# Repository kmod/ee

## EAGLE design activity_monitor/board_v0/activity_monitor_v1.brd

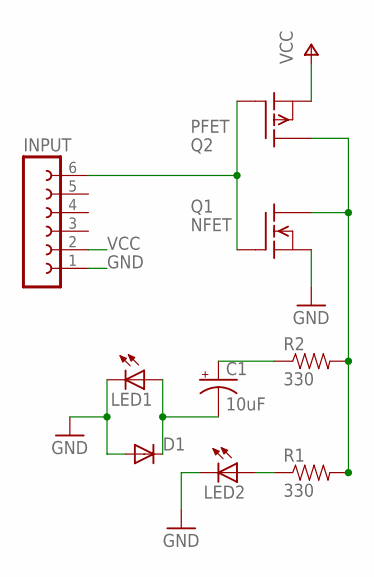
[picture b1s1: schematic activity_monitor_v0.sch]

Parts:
C1: 10uF; CPOL-RADIAL-10UF-25V
D1: 1N4004; DO41-10
INPUT: FE06-1; FE06
LED1, LED2: LED5MM
Q1: NFET; TO220
Q2: PFET; TO220
R1, R2: 330; AXIAL-0.3

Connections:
44: INPUT.6, Q1.1 (G), Q2.1 (G)
GND: D1.A, INPUT.1, LED1.K (C), LED2.K (C), Q1.3 (S)
unnamed: LED2.A, R1.P$1 (1)
unnamed: C1.1 (+), R2.P$1 (1)
unnamed: C1.2 (-), D1.C, LED1.A
unnamed: Q1.2 (D), Q2.2 (D), R1.P$2 (2), R2.P$2 (2)
VCC: INPUT.2, Q2.3 (S)

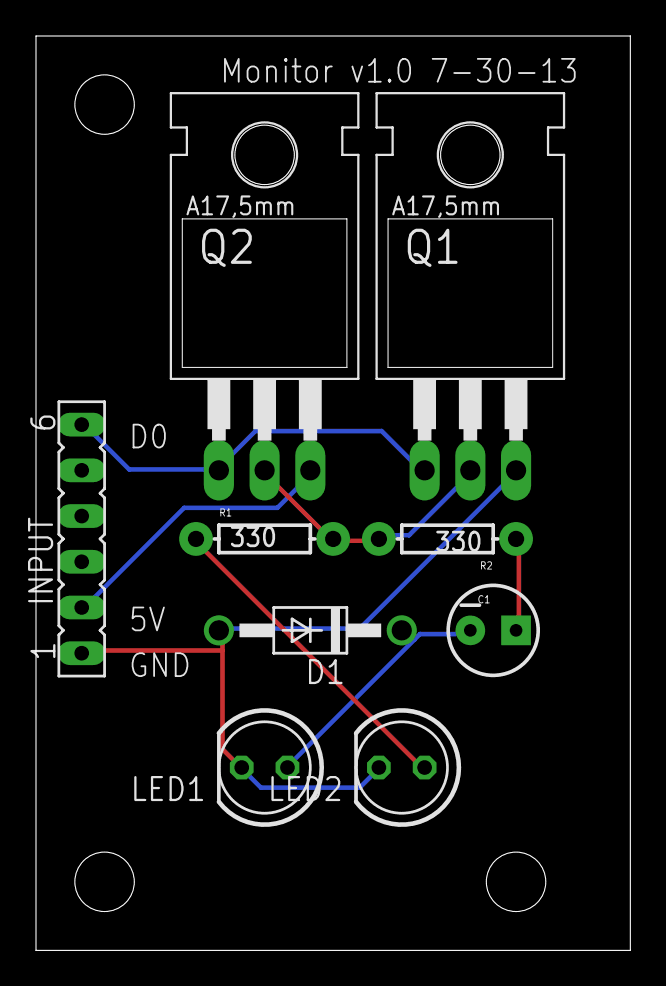
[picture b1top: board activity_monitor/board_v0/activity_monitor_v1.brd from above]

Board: 2 copper layers, 33.0 x 50.8 mm, 12 parts (0 on the bottom side), 7 nets.

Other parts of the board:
U$1, U$2, U$3: STAND-OFF

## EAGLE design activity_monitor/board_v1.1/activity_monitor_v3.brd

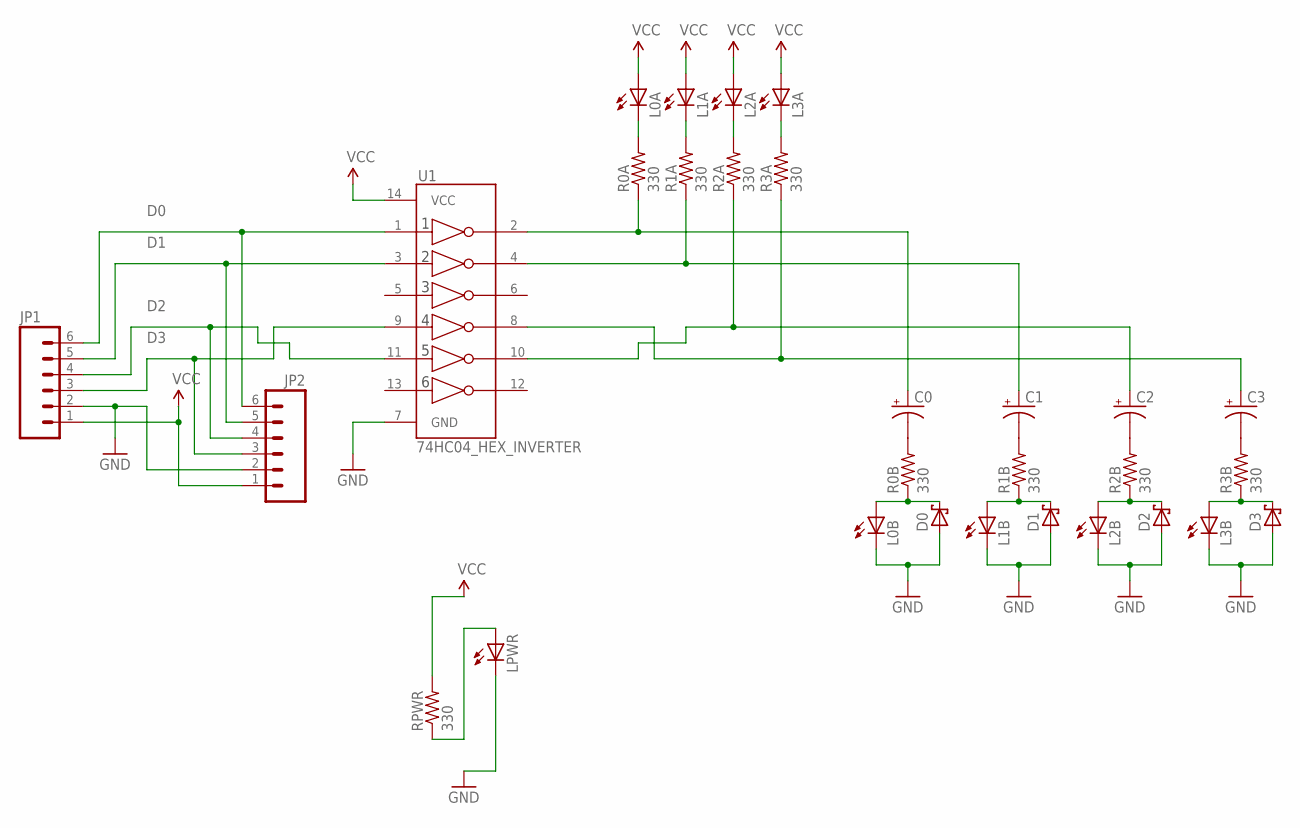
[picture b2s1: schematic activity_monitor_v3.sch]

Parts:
C0, C1, C2, C3: 10UF-TANT; EIA3216
D0, D1, D2, D3: SCHOTTKY-DIODEDO35-7; DO35-7
JP1, JP2: M06SIP; 1X06
L0A, L0B, L1A, L1B, L2A, L2B, L3A, L3B: LED0603; LED-0603
LPWR: LED0603; LED-0603
R0A, R0B, R1A, R1B, R2A, R2B, R3A, R3B: 330; 0603-RES
RPWR: 330; 0603-RES
U1: 74HC04_HEX_INVERTER; DIL14

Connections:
D0: JP1.6, JP2.6, U1.1 (1A)
D1: JP1.5, JP2.5, U1.3 (2A)
D2: JP1.4, JP2.4, U1.11 (5A)
D3: JP1.3, JP2.3, U1.9 (4A)
GND: D0.A, D1.A, D2.A, D3.A, JP1.2, JP2.2, L0B.C, L1B.C, L2B.C, L3B.C, LPWR.C, U1.7 (GND)
unnamed: C0.A (+), R0A.1, U1.2 (1Y)
unnamed: C1.A (+), R1A.1, U1.4 (2Y)
unnamed: C2.A (+), R2A.1, U1.10 (5Y)
unnamed: C3.A (+), R3A.1, U1.8 (4Y)
unnamed: L0A.C, R0A.2
unnamed: L1A.C, R1A.2
unnamed: L2A.C, R2A.2
unnamed: L3A.C, R3A.2
unnamed: C0.C (-), R0B.2
unnamed: D0.C, L0B.A, R0B.1
unnamed: C1.C (-), R1B.2
unnamed: LPWR.A, RPWR.1
unnamed: C2.C (-), R2B.2
unnamed: C3.C (-), R3B.2
R1B: D1.C, L1B.A, R1B.1
R2B: D2.C, L2B.A, R2B.1
R3B: D3.C, L3B.A, R3B.1
VCC: JP1.1, JP2.1, L0A.A, L1A.A, L2A.A, L3A.A, RPWR.2, U1.14 (VCC)

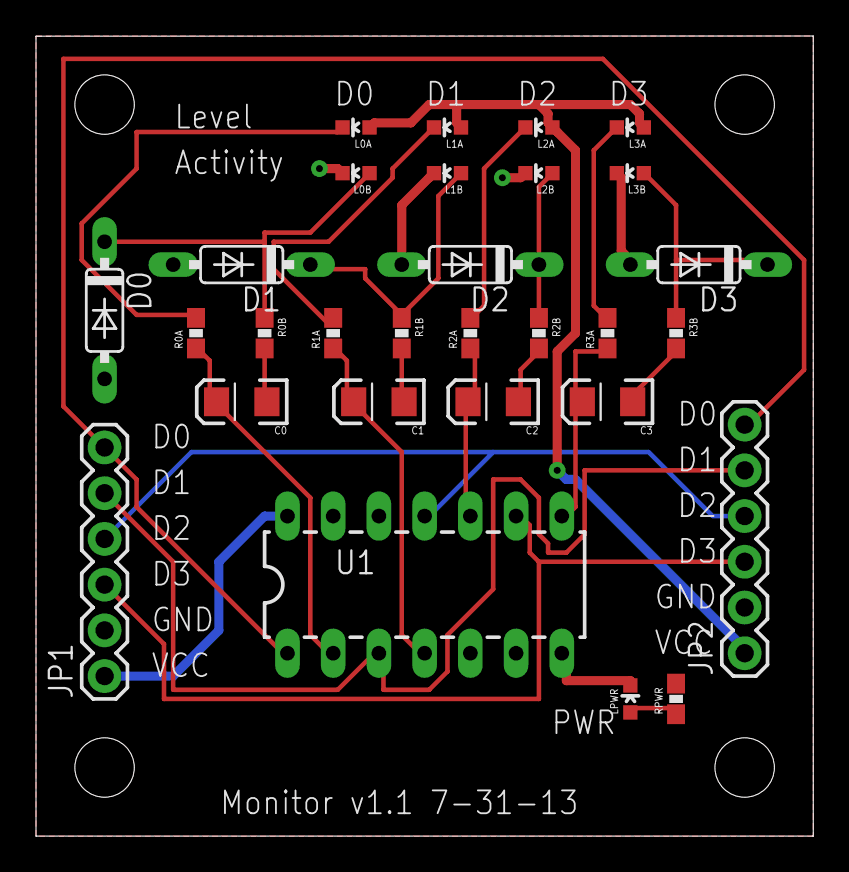
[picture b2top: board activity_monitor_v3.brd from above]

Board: 2 copper layers, 43.2 x 44.5 mm, 33 parts (0 on the bottom side), 23 nets.

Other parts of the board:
U$1, U$2, U$3, U$4: STAND-OFF

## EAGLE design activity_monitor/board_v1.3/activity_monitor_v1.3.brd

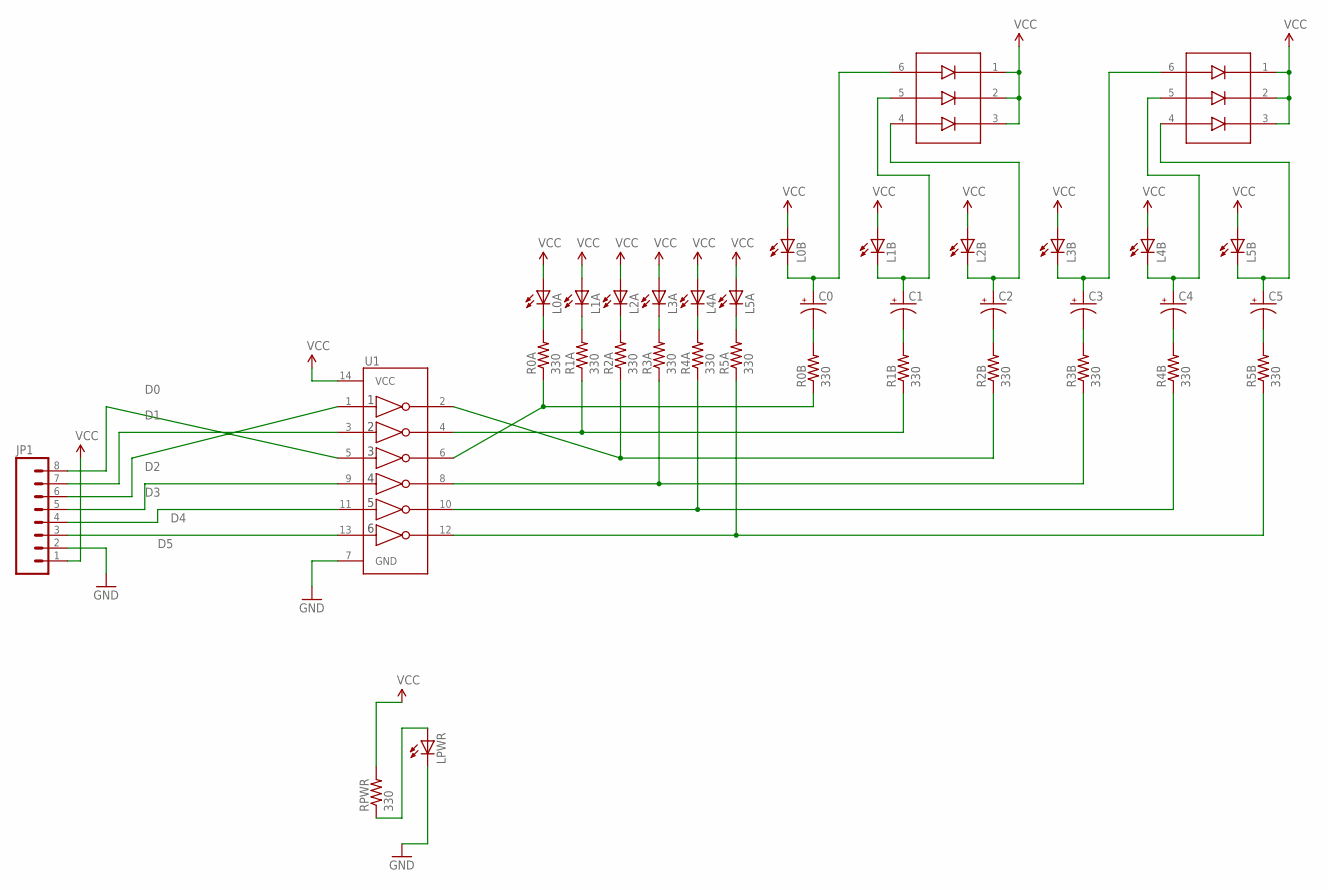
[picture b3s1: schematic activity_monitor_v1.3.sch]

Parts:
C0, C1, C2, C3, C4, C5: 10UF-TANT; EIA3216
JP1: M081X08; 1X08
L0A, L0B, L1A, L1B, L2A, L2B, L3A, L3B, L4A, L4B, L5A, L5B: LED0603; 0603_LED
LPWR: LED0603; 0603_LED
R0A, R0B, R1A, R1B, R2A, R2B, R3A, R3B, R4A, R4B, R5A, R5B: 330; 0603-RES
RPWR: 330; 0603-RES
U1: 74HC04_HEX_INVERTERTSSOP14; TSSOP14
U$1, U$2: SD103ATW-7-F; SOT363

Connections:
D0: JP1.8, U1.5 (3A)
D1: JP1.7, U1.3 (2A)
D2: JP1.6, U1.1 (1A)
D3: JP1.5, U1.9 (4A)
D4: JP1.4, U1.11 (5A)
D5: JP1.3, U1.13 (6A)
GND: JP1.2, LPWR.C, U1.7 (GND)
unnamed: R0A.1, R0B.1, U1.6 (3Y)
unnamed: R1A.1, R1B.1, U1.4 (2Y)
unnamed: C5.C (-), R5B.2
unnamed: C4.C (-), R4B.2
unnamed: L0A.C, R0A.2
unnamed: L1A.C, R1A.2
unnamed: L2A.C, R2A.2
unnamed: L3A.C, R3A.2
unnamed: C3.C (-), R3B.2
unnamed: C0.A (+), L0B.C, U$1.6 (I1)
unnamed: L4A.C, R4A.2
unnamed: C2.C (-), R2B.2
unnamed: LPWR.A, RPWR.1
unnamed: L5A.C, R5A.2
unnamed: C1.C (-), R1B.2
unnamed: R2A.1, R2B.1, U1.2 (1Y)
unnamed: R3A.1, R3B.1, U1.8 (4Y)
unnamed: C0.C (-), R0B.2
unnamed: R4A.1, R4B.1, U1.10 (5Y)
unnamed: R5A.1, R5B.1, U1.12 (6Y)
unnamed: C1.A (+), L1B.C, U$1.5 (I2)
unnamed: C2.A (+), L2B.C, U$1.4 (I3)
unnamed: C3.A (+), L3B.C, U$2.6 (I1)
unnamed: C4.A (+), L4B.C, U$2.5 (I2)
unnamed: C5.A (+), L5B.C, U$2.4 (I3)
VCC: JP1.1, L0A.A, L0B.A, L1A.A, L1B.A, L2A.A, L2B.A, L3A.A, L3B.A, L4A.A, L4B.A, L5A.A, L5B.A, RPWR.2, U1.14 (VCC), U$1.1 (O1), U$1.2 (O2), U$1.3 (O3), U$2.1 (O1), U$2.2 (O2), U$2.3 (O3)

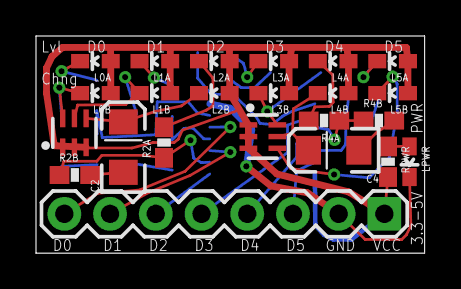
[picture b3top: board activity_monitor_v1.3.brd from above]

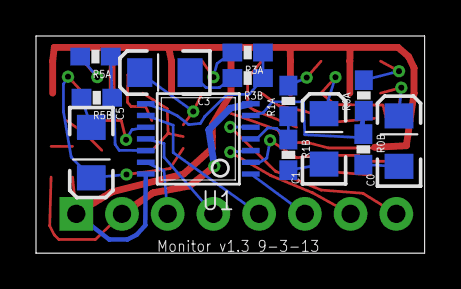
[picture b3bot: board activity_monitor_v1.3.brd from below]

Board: 2 copper layers, 21.6 x 12.1 mm, 36 parts (13 on the bottom side), 33 nets.

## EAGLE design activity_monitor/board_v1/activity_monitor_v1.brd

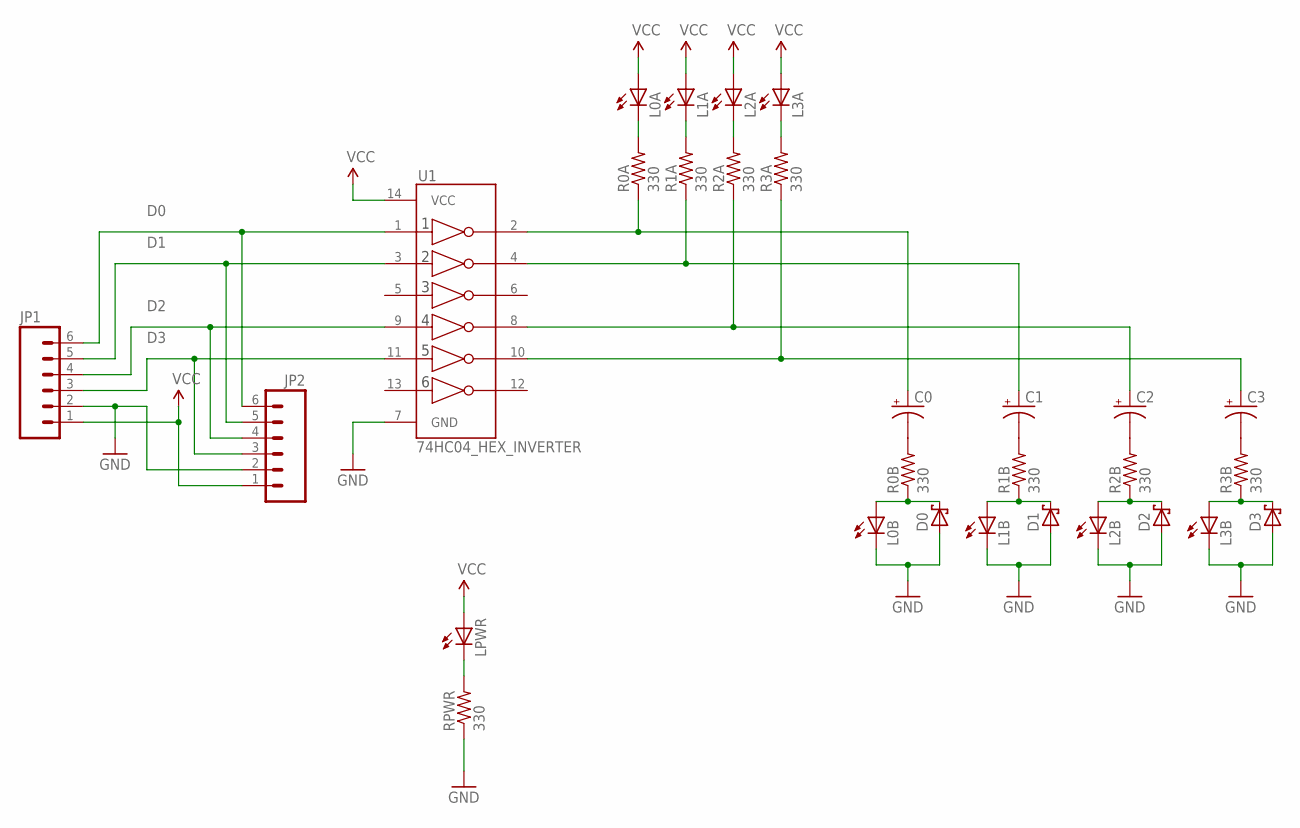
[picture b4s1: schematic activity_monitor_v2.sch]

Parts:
C0, C1, C2, C3: CAP_POLPTH2; CPOL-RADIAL-10UF-25V
D0, D1, D2, D3: SCHOTTKY-DIODEDO35-7; DO35-7
JP1, JP2: M06SIP; 1X06
L0A, L0B, L1A, L1B, L2A, L2B, L3A, L3B: LED3MM
LPWR: LED3MM
R0A, R0B, R1A, R1B, R2A, R2B, R3A, R3B: 330; AXIAL-0.4
RPWR: 330; AXIAL-0.4
U1: 74HC04_HEX_INVERTER; DIL14

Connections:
D0: JP1.6, JP2.6, U1.1 (1A)
D1: JP1.5, JP2.5, U1.3 (2A)
D2: JP1.4, JP2.4, U1.9 (4A)
D3: JP1.3, JP2.3, U1.11 (5A)
GND: D0.A, D1.A, D2.A, D3.A, JP1.2, JP2.2, L0B.K (C), L1B.K (C), L2B.K (C), L3B.K (C), RPWR.P$1 (1), U1.7 (GND)
unnamed: C0.1 (+), R0A.P$1 (1), U1.2 (1Y)
unnamed: C1.1 (+), R1A.P$1 (1), U1.4 (2Y)
unnamed: C2.1 (+), R2A.P$1 (1), U1.8 (4Y)
unnamed: C3.1 (+), R3A.P$1 (1), U1.10 (5Y)
unnamed: L0A.K (C), R0A.P$2 (2)
unnamed: L1A.K (C), R1A.P$2 (2)
unnamed: L2A.K (C), R2A.P$2 (2)
unnamed: L3A.K (C), R3A.P$2 (2)
unnamed: C0.2 (-), R0B.P$2 (2)
unnamed: D0.C, L0B.A, R0B.P$1 (1)
unnamed: C1.2 (-), R1B.P$2 (2)
unnamed: LPWR.K (C), RPWR.P$2 (2)
unnamed: C2.2 (-), R2B.P$2 (2)
unnamed: C3.2 (-), R3B.P$2 (2)
R1B: D1.C, L1B.A, R1B.P$1 (1)
R2B: D2.C, L2B.A, R2B.P$1 (1)
R3B: D3.C, L3B.A, R3B.P$1 (1)
VCC: JP1.1, JP2.1, L0A.A, L1A.A, L2A.A, L3A.A, LPWR.A, U1.14 (VCC)

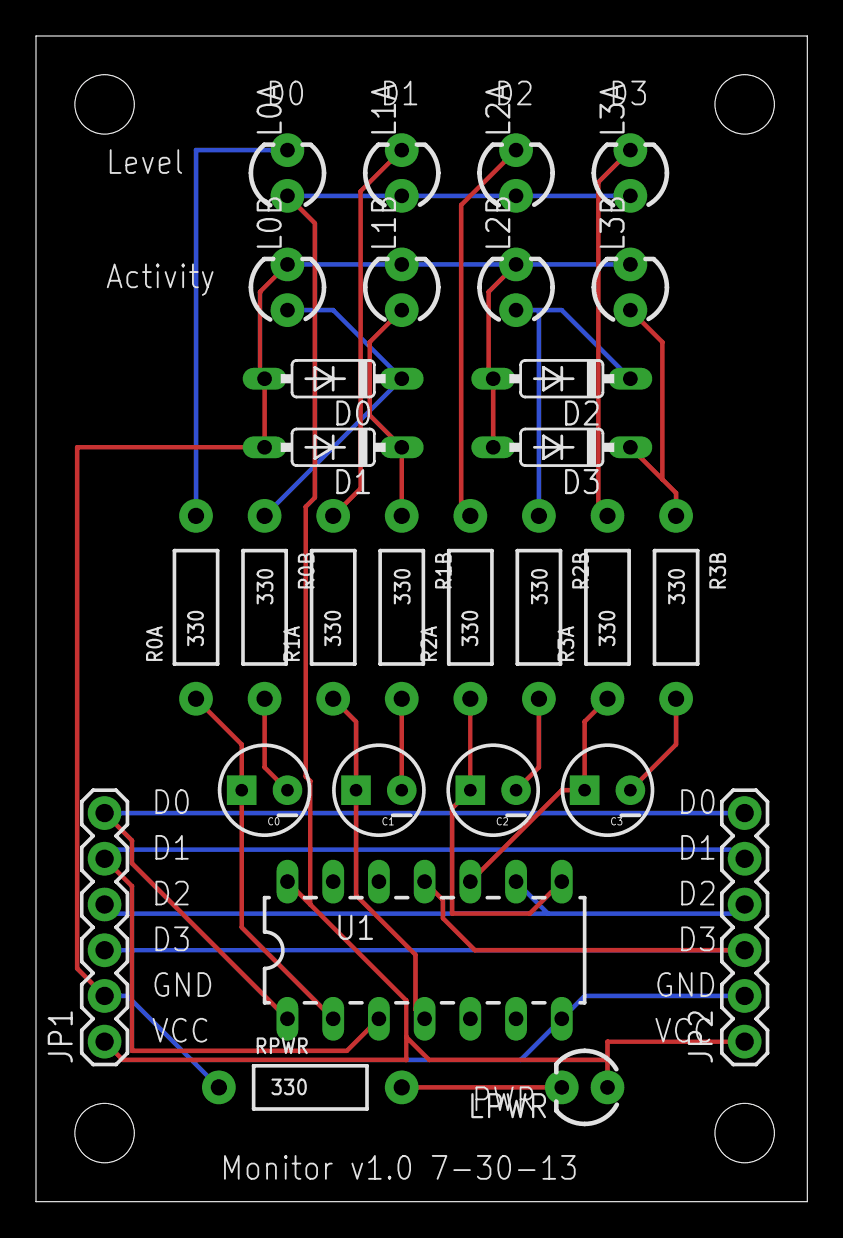
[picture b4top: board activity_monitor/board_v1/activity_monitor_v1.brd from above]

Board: 2 copper layers, 42.9 x 64.8 mm, 33 parts (0 on the bottom side), 23 nets.

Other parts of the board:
U$1, U$2, U$3, U$4: STAND-OFF

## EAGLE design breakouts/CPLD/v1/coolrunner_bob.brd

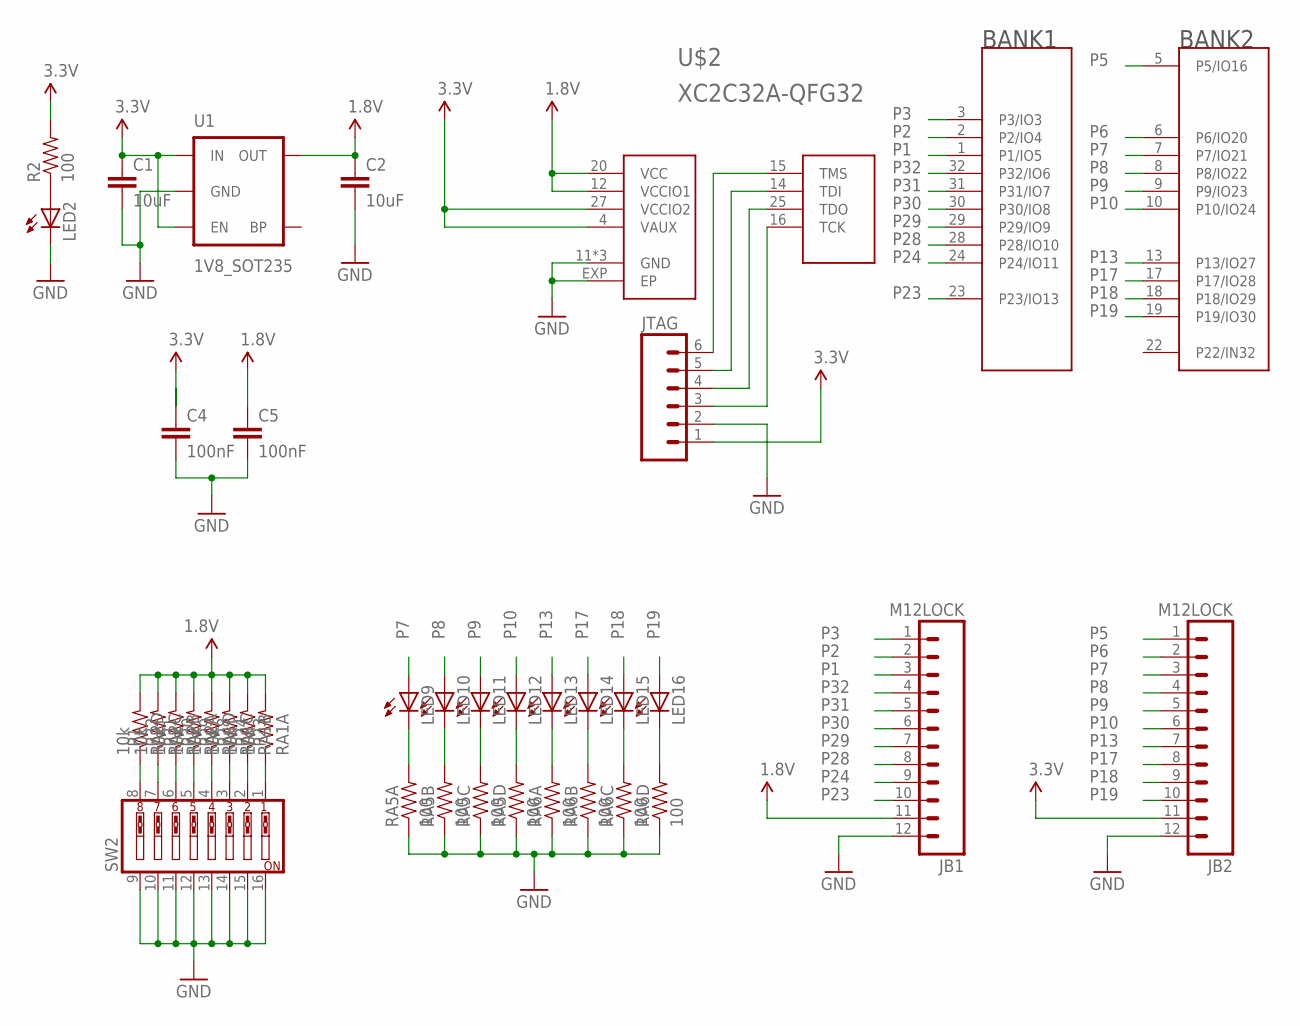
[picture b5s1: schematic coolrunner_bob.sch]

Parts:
C1, C2: 10uF; 0805
C4, C5: 100nF; 0402-CAP
JB1, JB2: M12LOCK; 1X12_LOCK
JTAG: M06LOCK; 1X06_LOCK
LED2, LED9, LED10, LED11, LED12, LED13, LED14, LED15, LED16: LED0603; LED-0603
R2: 100; 0603-RES
RA1, RA2: 10k; 0603-ARV
RA5, RA6: 100; 0603-ARV
SW2: SW_DIP-8; DIPSWITCH-08
U1: 1V8_SOT235; SOT23-5
U$2: XC2C32A-QFG32; QFN32-5X5

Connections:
1.8V: C2.1, C5.1, JB1.11, RA1.5 (2), RA1.6 (2), RA1.7 (2), RA1.8 (2), RA2.5 (2), RA2.6 (2), RA2.7 (2), RA2.8 (2), U1.5 (OUT), U$2.12 (VCCIO1), U$2.20 (VCC)
3.3V: C1.1, C4.1, JB2.11, JTAG.1, R2.2, U1.1 (IN), U1.3 (EN), U$2.4 (VAUX), U$2.27 (VCCIO2)
GND: C1.2, C2.2, C4.2, C5.2, JB1.12, JB2.12, JTAG.2, LED2.C, RA5.1, RA5.2 (1), RA5.3 (1), RA5.4 (1), RA6.1, RA6.2 (1), RA6.3 (1), RA6.4 (1), SW2.9, SW2.10, SW2.11, SW2.12, SW2.13, SW2.14, SW2.15, SW2.16, U1.2 (GND), U$2.11 (GND), U$2.21 (GND), U$2.26 (GND), U$2.EXP (EP)
unnamed: LED2.A, R2.1
unnamed: LED16.C, RA6.5 (2)
unnamed: LED15.C, RA6.6 (2)
unnamed: LED14.C, RA6.7 (2)
unnamed: LED13.C, RA6.8 (2)
unnamed: LED12.C, RA5.5 (2)
unnamed: LED11.C, RA5.6 (2)
unnamed: LED10.C, RA5.7 (2)
unnamed: LED9.C, RA5.8 (2)
P1: JB1.3, RA2.4 (1), SW2.8, U$2.1 (P1/IO5)
P2: JB1.2, U$2.2 (P2/IO4)
P3: JB1.1, U$2.3 (P3/IO3)
P5: JB2.1, U$2.5 (P5/IO16)
P6: JB2.2, U$2.6 (P6/IO20)
P7: JB2.3, LED9.A, U$2.7 (P7/IO21)
P8: JB2.4, LED10.A, U$2.8 (P8/IO22)
P9: JB2.5, LED11.A, U$2.9 (P9/IO23)
P10: JB2.6, LED12.A, U$2.10 (P10/IO24)
P13: JB2.7, LED13.A, U$2.13 (P13/IO27)
P17: JB2.8, LED14.A, U$2.17 (P17/IO28)
P18: JB2.9, LED15.A, U$2.18 (P18/IO29)
P19: JB2.10, LED16.A, U$2.19 (P19/IO30)
P23: JB1.10, RA1.1, SW2.1, U$2.23 (P23/IO13)
P24: JB1.9, RA1.2 (1), SW2.2, U$2.24 (P24/IO11)
P28: JB1.8, RA1.3 (1), SW2.3, U$2.28 (P28/IO10)
P29: JB1.7, RA1.4 (1), SW2.4, U$2.29 (P29/IO9)
P30: JB1.6, RA2.1, SW2.5, U$2.30 (P30/IO8)
P31: JB1.5, RA2.2 (1), SW2.6, U$2.31 (P31/IO7)
P32: JB1.4, RA2.3 (1), SW2.7, U$2.32 (P32/IO6)
TCK: JTAG.3, U$2.16 (TCK)
TDI: JTAG.5, U$2.14 (TDI)
TDO: JTAG.4, U$2.25 (TDO)
TMS: JTAG.6, U$2.15 (TMS)

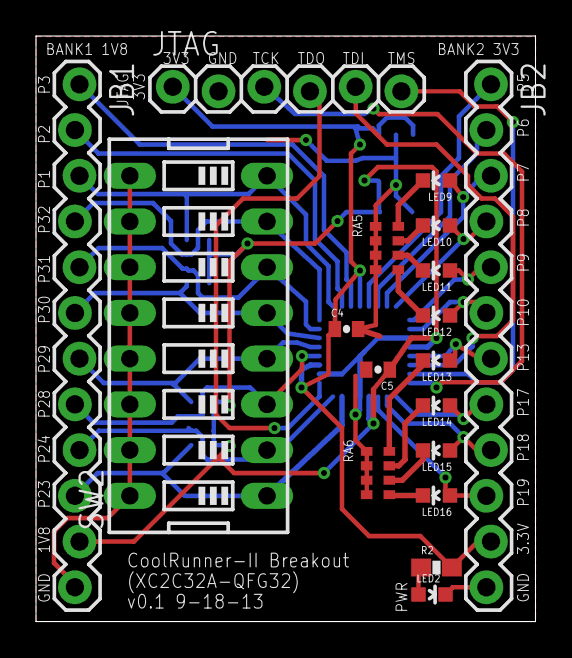
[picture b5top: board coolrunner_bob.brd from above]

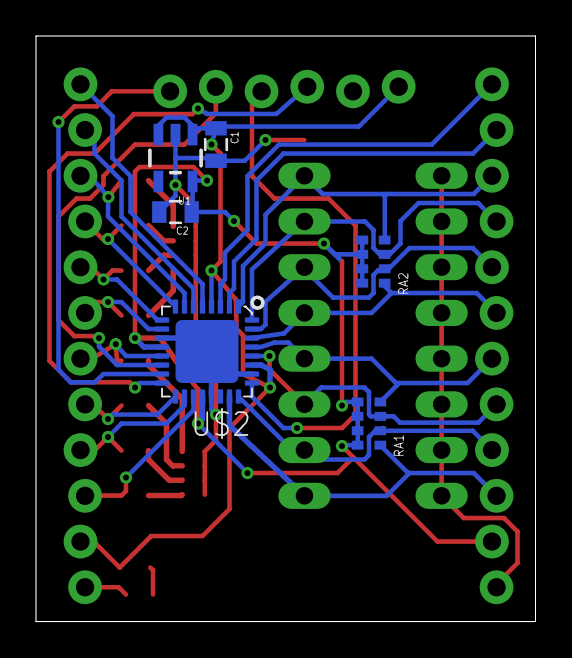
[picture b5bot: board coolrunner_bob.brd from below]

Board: 2 copper layers, 27.8 x 32.5 mm, 24 parts (6 on the bottom side), 36 nets.

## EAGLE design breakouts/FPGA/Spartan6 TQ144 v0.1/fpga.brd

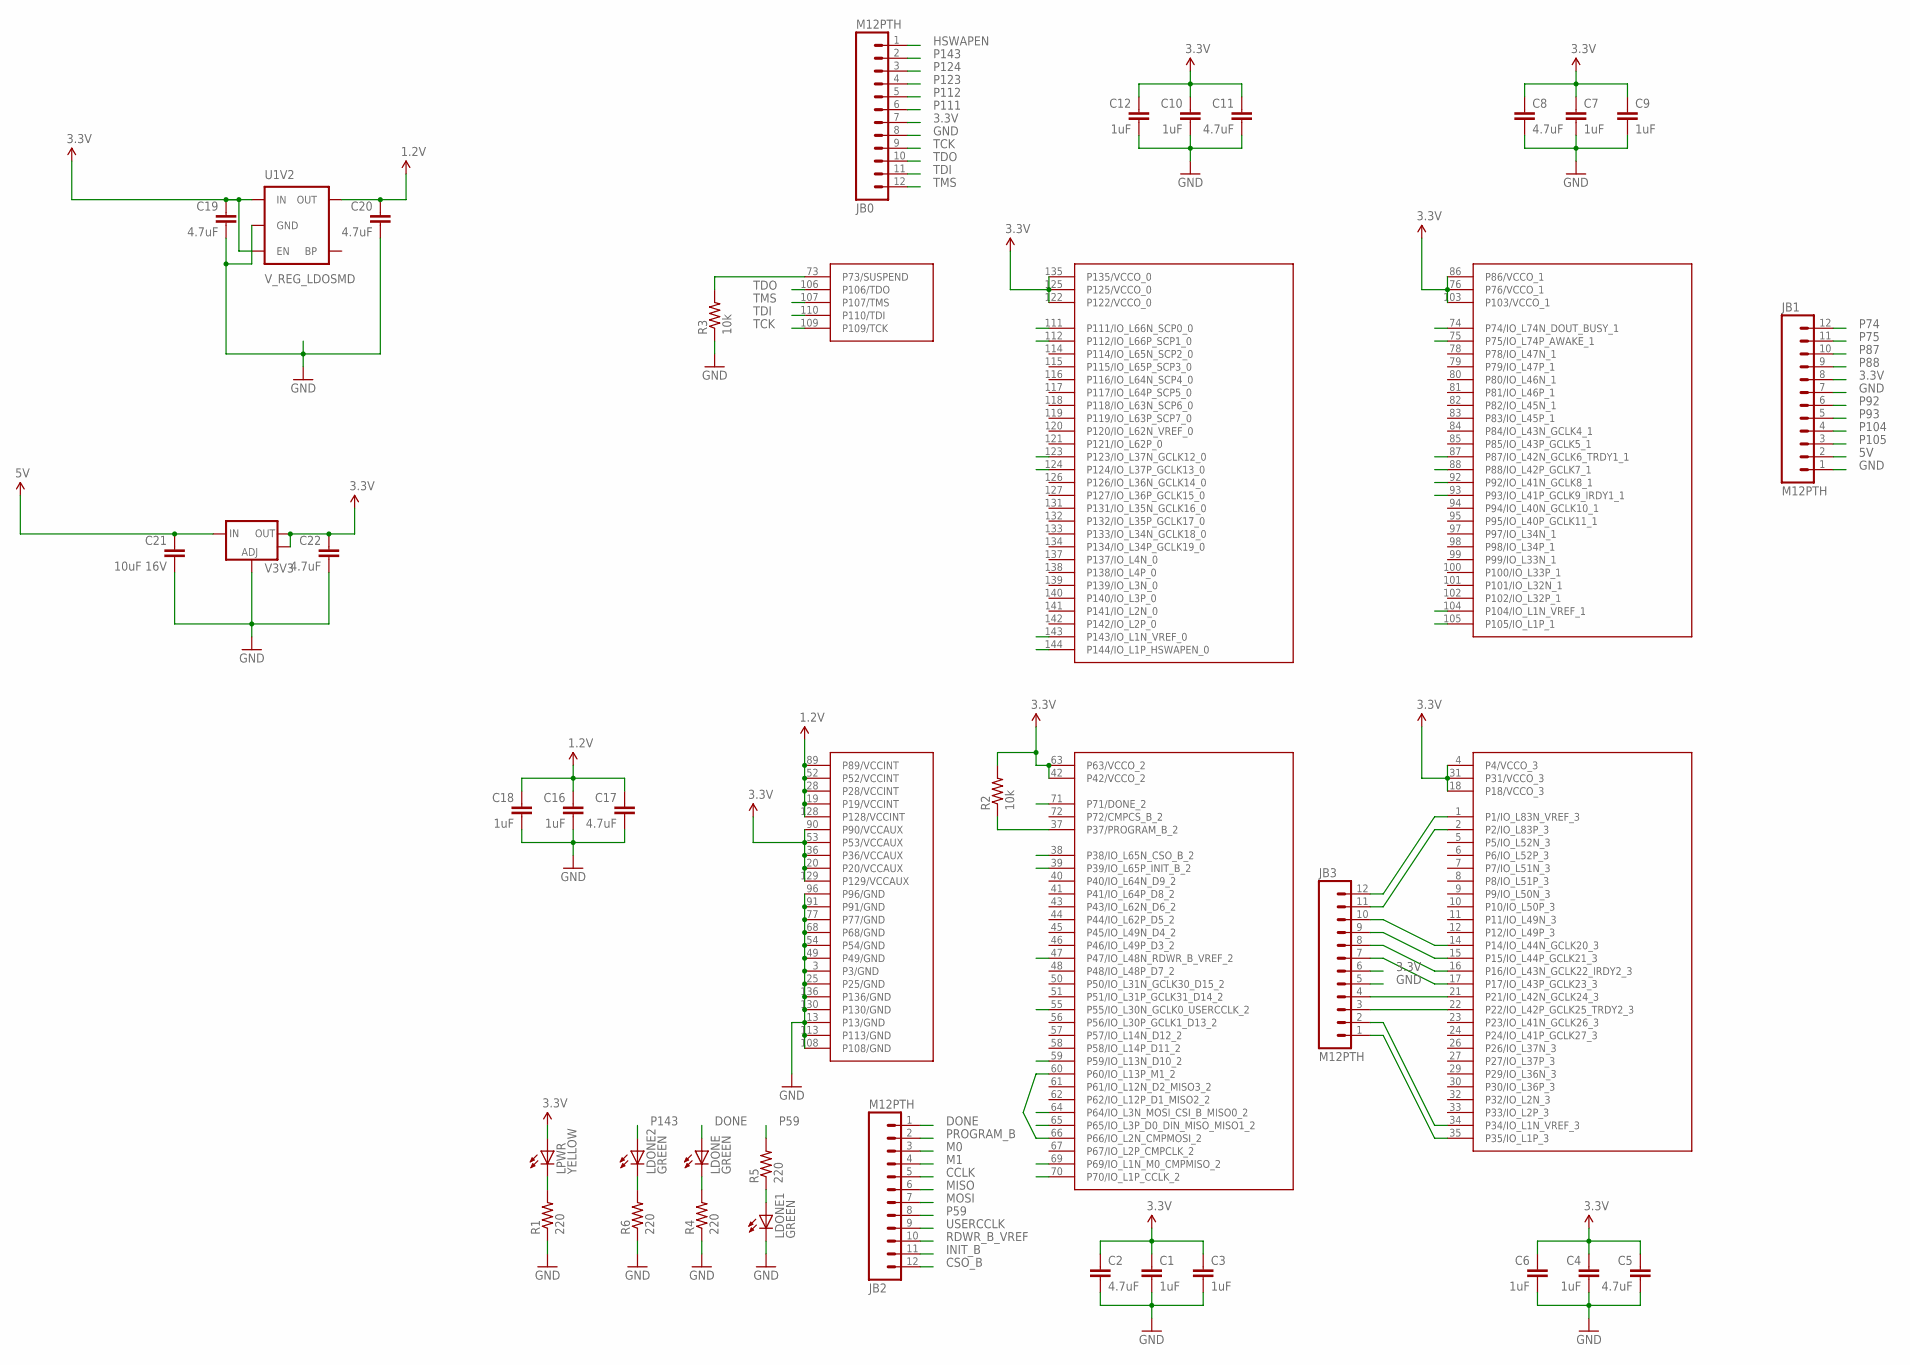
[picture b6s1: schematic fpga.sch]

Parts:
C1, C3, C4, C6, C7, C9, C10, C12, C16, C18: 1uF; 0402-CAP
C2, C5, C8, C11, C17, C19, C20, C22: 4.7uF; 0805
C21: 10uF 16V; 0805
JB0, JB1, JB2, JB3: M12PTH; 1X12
LDONE, LDONE1, LDONE2: GREEN; 0603_LED
LPWR: YELLOW; 0603_LED
R1, R4, R5, R6: 220; 0603-RES
R2, R3: 10k; 0603-RES
U1V2: V_REG_LDOSMD; SOT23-5
U$1: XC6SLX-TQ144; XILNX_TQ144
V3V3: V_REG_LM1117SOT223; SOT223

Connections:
1.2V: C16.1, C17.1, C18.1, C20.1, U1V2.5 (OUT), U$1.19 (P19/VCCINT), U$1.28 (P28/VCCINT), U$1.52 (P52/VCCINT), U$1.89 (P89/VCCINT), U$1.128 (P128/VCCINT)
3.3V: C1.1, C2.1, C3.1, C4.1, C5.1, C6.1, C7.1, C8.1, C9.1, C10.1, C11.1, C12.1, C19.1, C22.1, JB0.7, JB1.8, JB3.6, LPWR.A, R2.2, U1V2.1 (IN), U1V2.3 (EN), U$1.4 (P4/VCCO_3), U$1.18 (P18/VCCO_3), U$1.20 (P20/VCCAUX), U$1.31 (P31/VCCO_3), U$1.36 (P36/VCCAUX), U$1.42 (P42/VCCO_2), U$1.53 (P53/VCCAUX), U$1.63 (P63/VCCO_2), U$1.76 (P76/VCCO_1), U$1.86 (P86/VCCO_1), U$1.90 (P90/VCCAUX), U$1.103 (P103/VCCO_1), U$1.122 (P122/VCCO_0), U$1.125 (P125/VCCO_0), U$1.129 (P129/VCCAUX), U$1.135 (P135/VCCO_0), V3V3.2 (OUT), V3V3.4 (OUT)
5V: C21.1, JB1.2, V3V3.3 (IN)
CCLK: JB2.5, U$1.70 (P70/IO_L1P_CCLK_2)
CSO_B: JB2.12, U$1.38 (P38/IO_L65N_CSO_B_2)
DONE: JB2.1, LDONE.A, U$1.71 (P71/DONE_2)
GND: C1.2, C2.2, C3.2, C4.2, C5.2, C6.2, C7.2, C8.2, C9.2, C10.2, C11.2, C12.2, C16.2, C17.2, C18.2, C19.2, C20.2, C21.2, C22.2, JB0.8, JB1.1, JB1.7, JB3.5, LDONE1.C, R1.1, R3.1, R4.1, R6.1, U1V2.2 (GND), U$1.3 (P3/GND), U$1.13 (P13/GND), U$1.25 (P25/GND), U$1.49 (P49/GND), U$1.54 (P54/GND), U$1.68 (P68/GND), U$1.77 (P77/GND), U$1.91 (P91/GND), U$1.96 (P96/GND), U$1.108 (P108/GND), U$1.113 (P113/GND), U$1.130 (P130/GND), U$1.136 (P136/GND), V3V3.1 (ADJ)
HSWAPEN: JB0.1, U$1.144 (P144/IO_L1P_HSWAPEN_0)
INIT_B: JB2.11, U$1.39 (P39/IO_L65P_INIT_B_2)
M0: JB2.3, U$1.69 (P69/IO_L1N_M0_CMPMISO_2)
M1: JB2.4, U$1.60 (P60/IO_L13P_M1_2), U$1.66 (P66/IO_L2N_CMPMOSI_2)
MISO: JB2.6, U$1.65 (P65/IO_L3P_D0_DIN_MISO_MISO1_2)
MOSI: JB2.7, U$1.64 (P64/IO_L3N_MOSI_CSI_B_MISO0_2)
unnamed: LDONE1.A, R5.1
unnamed: LPWR.C, R1.2
unnamed: LDONE.C, R4.2
unnamed: LDONE2.C, R6.2
unnamed: R3.2, U$1.73 (P73/SUSPEND)
P1: JB3.12, U$1.1 (P1/IO_L83N_VREF_3)
P2: JB3.11, U$1.2 (P2/IO_L83P_3)
P14: JB3.10, U$1.14 (P14/IO_L44N_GCLK20_3)
P15: JB3.9, U$1.15 (P15/IO_L44P_GCLK21_3)
P16: JB3.8, U$1.16 (P16/IO_L43N_GCLK22_IRDY2_3)
P17: JB3.7, U$1.17 (P17/IO_L43P_GCLK23_3)
P21: JB3.4, U$1.21 (P21/IO_L42N_GCLK24_3)
P22: JB3.3, U$1.22 (P22/IO_L42P_GCLK25_TRDY2_3)
P34: JB3.2, U$1.34 (P34/IO_L1N_VREF_3)
P35: JB3.1, U$1.35 (P35/IO_L1P_3)
P59: JB2.8, R5.2, U$1.59 (P59/IO_L13N_D10_2)
P74: JB1.12, U$1.74 (P74/IO_L74N_DOUT_BUSY_1)
P75: JB1.11, U$1.75 (P75/IO_L74P_AWAKE_1)
P87: JB1.10, U$1.87 (P87/IO_L42N_GCLK6_TRDY1_1)
P88: JB1.9, U$1.88 (P88/IO_L42P_GCLK7_1)
P92: JB1.6, U$1.92 (P92/IO_L41N_GCLK8_1)
P93: JB1.5, U$1.93 (P93/IO_L41P_GCLK9_IRDY1_1)
P104: JB1.4, U$1.104 (P104/IO_L1N_VREF_1)
P105: JB1.3, U$1.105 (P105/IO_L1P_1)
P111: JB0.6, U$1.111 (P111/IO_L66N_SCP0_0)
P112: JB0.5, U$1.112 (P112/IO_L66P_SCP1_0)
P123: JB0.4, U$1.123 (P123/IO_L37N_GCLK12_0)
P124: JB0.3, U$1.124 (P124/IO_L37P_GCLK13_0)
P143: JB0.2, LDONE2.A, U$1.143 (P143/IO_L1N_VREF_0)
PROGRAM_B: JB2.2, R2.1, U$1.37 (P37/PROGRAM_B_2)
RDWR_B_VREF: JB2.10, U$1.47 (P47/IO_L48N_RDWR_B_VREF_2)
TCK: JB0.9, U$1.109 (P109/TCK)
TDI: JB0.11, U$1.110 (P110/TDI)
TDO: JB0.10, U$1.106 (P106/TDO)
TMS: JB0.12, U$1.107 (P107/TMS)
USERCCLK: JB2.9, U$1.55 (P55/IO_L30N_GCLK0_USERCCLK_2)

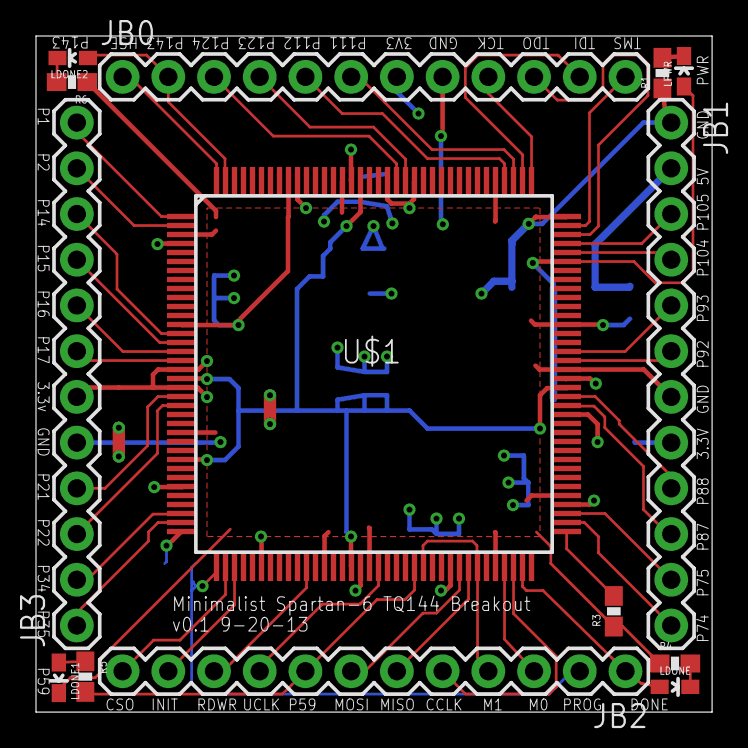
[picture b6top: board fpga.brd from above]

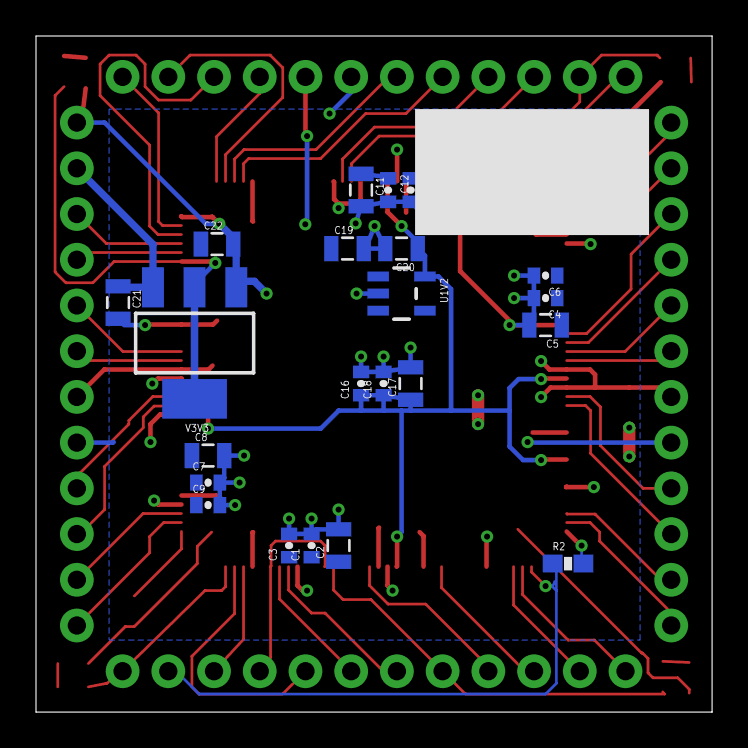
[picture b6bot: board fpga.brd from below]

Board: 2 copper layers, 37.6 x 37.6 mm, 36 parts (22 on the bottom side), 49 nets.

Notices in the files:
parts and their libraries:
SparkFun-Capacitors: Licensing: CC v3.0 Share-Alike You are welcome to use this library for commercial purposes.
